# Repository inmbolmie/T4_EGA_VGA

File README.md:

# T4_EGA_VGA

Teensy 4.0 based CGA/EGA to VGA converter

_**Second version with improved shielding and protection**_

This is my poor-man's RGBi to VGA converter that can be built with just a Teensy 4.0 and a bunch of resistors. Works quite well with low resolution modes and works also but with a little less quality with high resolution modes. MDA is not supported at this moment.

To make it work you need as a bare minimum the Teensy 4.0, a VGA cable, a DE9 cable, and 25 resistors of 5 different values, so it can be made very cheaply as a DIY project on a breadboard.

The objective of this project was building the converter using only the Teensy, so it lacks any CPLD or other complex sampling and level shifting interfaces that other better converters like MCE2VGA use.

For the VGA output signal generation it uses the awesome VGA_t4 library by Jean-Marc Harvengt  https://github.com/Jean-MarcHarvengt/VGA_t4, this project wouldn't be possible without it.

Before jumping in, be sure that you have read the **current limitations** section and watch the video for an idea of its performance.

## Operation

The converter needs to be USB-powered through the Teensy micro-USB connector, from a computer port of a regular wall USB power adapter. If possible, it is better to power up the converter before connecting it to the video source.

Once the converter is powered, just connect the DE9 end to the computer/graphics card through a suitable cable to convert, and the DE15 end to the VGA monitor that will display the converted video signal. The DE9 cable mush be straight and all the pins must be connected. Try to avoid null modem or other special cables that are not straight pin-to-pin.

**Please, don't program the Teensy while connected to either the DE9 or DE15 connector.**

## Supported modes

Supported modes and some comments about each one.

http://minuszerodegrees.net/video/bios_video_modes.htm

|Mode|Resolution|VGA resolution|Scanlines|Supported|HR Switch|CPU Speed|Remarks|
|---	|---	|---	|---	|---	|---	|---	|---	|
|0x00h|320x200 greyscale|320x200|no|Resistor network*|off|600Mhz|40 columns text mode|
|0x01h|320x200 color|320x200|no|Resistor network*|off|600Mhz|40 columns text mode|
|0x02h|640x200 greyscale|640x480|yes|Level converter*|on|984Mhz|80 columns text mode|
|0x03h|640x200 color|640x480|yes|Level converter*|on|984Mhz|80 columns text mode|
|0x04h|320x200 color|320x200|no|Resistor network*|off|600Mhz|4 color CGA graphics|
|0x05h|320x200 greyscale|320x200|no|Resistor network*|off|600Mhz|4 gray CGA graphics|
|0x06h|640x200 monochrome|640x480|yes|Level converter*|on|984Mhz|CGA high res monochrome|
|0x07h|720x350 monochrome|NOT SUPPORTED|NOT SUPPORTED|NOT SUPPORTED|NOT SUPPORTED|NOT SUPPORTED|MDA monochrome mode|
|0x08h|160x200 color|UNTESTED|UNTESTED|UNTESTED|UNTESTED|UNTESTED|PCjr. mode, should work but untested|
|0x09h|320x200 color|UNTESTED|UNTESTED|UNTESTED|UNTESTED|UNTESTED|PCjr. mode, should work but untested|
|0x0Ah|640x200 color|UNTESTED|UNTESTED|UNTESTED|UNTESTED|UNTESTED|PCjr. mode, should work but untested|
|0x0Dh|320x200 color|320x200|no|Resistor network*|off|600Mhz|EGA 16 color low resolution|
|0x0Eh|640x200 color|640x480|yes|Level converter*|on|984Mhz|EGA 16 color high resolution|
|0x0Fh|640x350 monochrome|640x480|no|Level converter*|both|984Mhz|EGA monochrome ultra-high resolution|
|0x10h|640x350 color|640x480|no|Level converter*|both|984Mhz|EGA 16 color ultra-high resolution|

Notes:

**Resistor Network** This mode works with both board versions, with resistor network capture or level converter

**Level converter** This mode may work somehow with resistor network capture, but gives best results with the level converter version

## Screenshots

Some screenshots for the different supported modes. They are taken simply with a smartphone pointing to a modern IPS monitor, so the alignment isn't perfect but they can give and idea about how it works. The computer driving the display is an IBM 5160 with a Paradise EGA card.

## Videos

Video showing 350 lines text mode, the Checkit graphic tests, Monkey Island and Commander Keen in 320x200x16 mode and PlanetX3 in 640x350x16 mode. Yes, Monkey Island is slow, but that is because it is running in a poor IBM 5160, the converter operates always at the full 60Hz.

https://youtu.be/SZSuXO_p2-U

## Controls.

There are 4 buttons and 1 switch that can be used to adjust the converter operation. Those are optional and not strictly required for basic operation.

* **HR ON/OFF switch  (pin 14)**. When on, the 640x200 graphic and 80 columns text modes are enabled. That is needed because the signal specs for 320x200 and 640x200 modes are exactly the same, so the converter would have a bad day to try to distinguish between them. With the switch ON, 320x200 will work the same, but with the switch OFF 320x200 will work better and the Teensy will operate at stock speed (600Mhz) and wouldn't even need extra cooling.
* **Pixel adjustment decrease (pin 6)**. Decrease 1 unit the pixel alignment. This makes the sampling start earlier and is like displacing the picture to the right
* **Pixel adjustment increase (pin 5)**. Increase 1 unit the pixel alignment. This makes the sampling start later and is like displacing the picture to the left
* **Store pixel alignment (pin 7)**. Hold this button for 2 seconds to store the current pixel value in EEPROM. The autodiscovery will be disabled for the current mode.
* **Reboot/Reset (pin 9)**. Push to reboot the Teensy. Hold for 2 seconds to erase all stored pixel alignment values and reboot, the autodiscovery will be enabled for all modes.

## Current limitations:

This is an experimental converter so some amount of pain is expected.

* **Instability**. The Teensy running at overclocking frequencies isn’t the most stable thing in the world. Some sudden reboots are to be expected. Also you will have to reboot the Teensy sometimes when changing between graphics modes. Keep it cool.

* **Noise**. sampling is not perfect and will lead to some pixel noise here and there.

* **Color smearing**. There is a limitation, especially in high res, due to the way VGA_t4 works separating the color bits between two concurrent DMA transfers. This can lead to a phase difference between the color components and visible color smearing more evident in high contrast pictures.

* **Lost pixels**. Currently some pixels are lost in the right side of the image. I think those are sacrificed to get better picture quality tweaking the DMA transfer values. This can be either OK or unacceptable to you. You can get the pixels back tuning some VGA_t4 magic numbers, but then color smearing is exacerbated.

* **Line wobbling**. There is also a problem in that the moment the VGA line start is generated  is not 100% exact and the lines can wobble a little. This is quite evident at about 2/3 of the screen horizontally.

* **Artifacts**. Sampling is affected by the ISR and some pixels and lines are lost in the process. This is very evident in the 15,7Khz modes as the VGA signal is 31,5 Khz, almost exactly double the frequency so the artifacts happen twice per line and the affected pixels in one line are more or less the same than the line before and after. This generates horizontal (entire lines lost) and diagonal (lost pixels) black lines in each individual sampled picture. Example of a single screen capture for a 15,7Khz mode:

Thankfully the VGA horizontal frequency is not EXACTLY double the input horizontal frequency, because in that case the affected pixels will be always the same and a slow moving vertical black band would be always present in the picture, or if the band were around the HSYNC area you will get absolutely no picture at all.

The 21,8Khz modes are less affected and there is no visible interference pattern in the picture. Example of a single screen capture for this mode, where the small horizontal lines are the pixels lost due to the ISR firing:

* **No 720px modes**. Unfortunately VGA_t4 at the moment doesn’t support any 720px mode, so MDA (720x350) is not supported. If we ever get that mode, MDA should be perfectly possible as the pixel clock is the same as EGA.

* **Needs alignment for every different card**.  The key to get a nice picture is adjusting the exact clock cycle after HSYNC where the converter starts sampling the signal. This point varies among different modes and different graphic cards. For my EGA card in CGA mode the point is quite different to a real CGA card. With a converter that operates oversampling, or for an analog monitor this is not a problem because you simply reposition the image horizontally, that is sometimes automatically done by the monitor itself. The converter tries to guess the optimal sampling point automatically looking for the first pixel in the image and remembering it afterwards, but this can fail in some cases, like:

    * There are no pixels in the first column
 
    * Noise leads to a fake first pixel detection and you lose part of the image forever
 
    * Some clever programmers generate borders around the image that are falsely interpreted as pixels. This happens for instance with Commander Keen. 

Because all of this, the user can store using the control switches a value that overrides the automatic calculation if needed.

* **Initial sync is slow**. The adapter needs to sync to signals and generate the sampling tables programmatically, so it’s not the fastest thing out there.

* **Probably won’t work well with some cards**. If some graphics card for any reason doesn’t keep a steady on-spec pixel clock, the converter will fail miserably and vertical noise bands will develop where the sampling gets out of alignment. In those cases you can try to tweak the magic numbers for the graphic modes (pixel period, etc) but that is an absolutely DIY task.

## Internal working

The converter captures the EGA/CGA signal using synchronous sampling. The program synchronizes its execution with the HSYNC signal and counts clock cycles until the arrival of each pixel, then it samples the color signals in parallel and maps each sample to its pixel using precalculated tables based in the data about the specific graphics mode that is capturing. The pixel is then color translated to the right palette and stored in a framebuffer before the arrival of the next sample.

In parallel, the VGA_t4 module manages the generation of the VGA signal from the framebuffer through the DMA resources of the Teensy using a timed ISR to initiate the DMA transfers. The DMA transfer pumps data from the framebuffer and generates the lines of the VGA signals. That happens in parallel with the sampling code execution, except for the ISR itself. 

The ISR interrupts the sampling code each time it fires, that is once or twice per line, so some synchronization code is needed to detect the signal sampling intervals affected by the ISR and discard those pixels and sometimes entire lines from the captured signal. This generates some visible artifacts, especially in fast moving or flashing scenes in the 15,7Khz modes, but it is unavoidable with this arrangement. Maybe a future Teensy would support 3 concurrent DMA channels for FlexIO pins or full 8 bit I/O for the available channels, so that sampling could be implemented also with DMA.

The Teensy needs to be overclocked to be able to sample at the insane pixel rates of high resolution modes, (16,257Mhz for the EGA 10h mode). At this moment, the 640x200 and 640x350 modes need to operate at 984Mhz. The program adjusts the Teensy speed automatically as required for the input mode detected. Low resolution modes (320x200) work well at stock speed (600Mhz).

## Building software

Simply build the sketch with Arduino with the Teensyduino addon installed https://www.pjrc.com/teensy/td_download.html and upload it to a Teensy 4.0 via USB cable. I’ve used Arduino 1.8.13 and Teensyduino 1.5.3. Be sure that you compile it for 600Mhz and “fastest” compiler optimization.

## Circuits

### VGA signal generation

On the physical side, the digital to analog conversion to generate the VGA RGB signals is done using a simple R2R resistor ladder.  VGA_t4 supports up to 8 bit color (with an experimental 12 bit mode), but to get the EGA palette you only need 6 bit color, so a 6 bit ladder with 2 bits per color channel is used. 

This is the formula I used to calculate the resistor values. The objective for each color signal is getting from the 3,3V of the Teensy a 1,4V maximum level and 75 ohm output impedance, that will get converted to 0,7V when connecting to the VGA monitor and its 75 ohm terminations.

https://www.wolframalpha.com/input/?i=R2%2F%28R2%2B%282*%28R1%2F3%29%29%29+%3D+%281.4%2F3.3%29%2C+2*R1*R2%2F%283*%28R2%2B%282*R1%2F3%29%29%29%3D75

Given that calculations, I took as the final resistor values:

* 130 ohm for R2
* 255 ohm for R1 
* 510 ohm for 2R1, 

That should be close enough to the theoretical values. You can even use two 510 ohm resistors in parallel instead of the 255 ohm, or two 255 ohm in series instead of the 510 ohm, so that one less resistor value is required. This won’t win any color accuracy competition, but should be good enough.

### EGA/CGA input capture

Unfortunately, for the EGA/CGA signal sampling we need to make voltage conversion, as EGA/CGA is TTL signalling with a 5V logic level, and the Teensy 4 only supports a maximum of 3,3V in its input pins. Give them the full 5V and you will fry the poor thing. 

To overcome that there are different possible solutions, and I have selected two, one using only a resistor network and the other making use of an active voltage converter.

### Version one: Cheapo resistor divider.

The true poor-man’s alternative. As the IBM CGA card line drivers are 74LS244 IC’s I calculate the minimum series resistor value from a (very optimistic, probably overestimated) 1mA maximum theoretical output current for the TTL gate. That gives for the 5V signal a maximum load of 5 Kohm. To get 3,3V from 5V through a 5K resistor divider you can use approximately a 1,5K and a 3K resistor.

This approach is cheap and easy, but it has the drawback that the resistors act like a RC network, slowing down the transitions between the high and low logical levels as the retain charge stored in the parasitic capacitance of the wires and the resistors themselves, that need to be discharged through the resistors. That flattens the signal and generates slow rising and falling edges that affect the sampling.

So with a resistor network you can expect the converter to operate like this:

* Low resolution (320X200 graphic and 40 columns text) modes work quite well. Pixel clock is around 8Mhz, slow enough for the resistor network to operate acceptably.

* High resolution text modes (80 columns) are usable with noise.    

* High resolution graphic modes work acceptable with less demanding games that doesn’t use complex graphics (like Thexder)

* High resolution graphic modes with more complex games like PlanetX3 (EGA version) work like crap. This is due to the fact that Planet X3 makes heavy use of dithering in high resolution modes, and that dithering generates a very high frequency in the color channels (16Mhz) that is basically too much for the resistor network.

If you are adventurous enough the quality can be quite improved lowering the resistor values, BUT that comes with the risk of overloading the line drivers of the graphics card or degrading the signal levels, so be warned if you try that.

Also be sure that you double check the resistor network wiring, as there is a risk the Teensy could receive the full 5V if something is wired up wrongly.

### Version two: TXS0108E voltage translator.

This is a popular bidirectional voltage translator for microcontrollers that theoretically can accept up to 55Mhz signals. It has just the 8 channels we need for the conversion (6 colors plus HSYNC and VSYNC). With this in place all the modes, high and low resolution work quite well. As it is popular it can be obtained very cheaply and you can even get it mounted in a nice ready to plug prototype board.

I’ve tried other solutions, none of which was fully satisfactory:

**74HCT245 driver @5V plus a lower value (500 ohm) resistor divider.** The 74HCT can drive higher loads than the 74LS so we can significantly lower the resistor values. Works well, but too cumbersome as you need the active component PLUS the resistors to make the 5V-3.3V conversion.

**74LVC245 driver @3,3V.** Too noisy, sampling gives terrible quality.

**74FCT244 driver**, quite rubbish sampling quality, didn’t work at all.

I haven’t tried one other possible solution, that is connect the signals to the Teensy through a single current limiting series resistor per channel. That is for the most adventurous out there, I haven’t tried because I don’t want to ruin my only Teensy board, but it should be possible if the right resistor value is low enough to get a good signal and high enough not to fry the Teensy. No idea of what that value should be.

## Schematics

### Schematic for version 1, TXS0108E based capture solution.

### Schematic for version 2, resistor based capture solution.

## Board fabrication

If you are crazy enough to make a real PCB for this, I provide the needed resources for the TXS0108E version, gerber file, bom and component placement for a popular online fabricator.

## Q&A:

**Is this better than a MCE2VGA?**

Definitely no, this is hackish and the MCE2VGA is very professional. You will have to adjust the sampling alignment all the time, the image quality is much worse and it supports less input modes and resolutions. Not to mention you can get a MCE2VGA tested, assembled and inside a nice 3D printed case for a reasonable amount of money.

**Should I use this as my main converter for my retro hardware?**

I see this as a nice weekend mini-project if you already have the Teensy, a bunch of resistors, you like it and you have no high expectations. I don’t recommend going for it as a standalone converter for general use.

**Why do you repeat so much code? Have you ever heard about functions and parameters?**

Of course I’ve heard, but in this case the code performance is absolutely critical. You have a fixed amount of clock cycles to process each sample before the next sample arrives. Some sections simply don’t work fast enough unless you use constants instead of variables, and reduce loops and logic checks to the bare minimum. And that is even more complicated by the VGA ISR firing all the time and interfering with the sampling. So I need/prefer to keep the modes all separated in code, despite 99% of that code being identical between different modes. Maybe some assembly code would help but actually it is working without needing any. Maybe that could make high resolution modes work at lower clock frequencies.

**Could this converter kill my beloved vintage graphics card/computer/monitor?**

Yes it can. I’ve not been able to test it with much hardware, I only have an IBM CGA card and a Paradise EGA card to test the converter, and with those it works flawlessly, but who knows with others.

**Could this converter kill my Teensy?**

High resolution modes work only with the Teensy overclocked at very high speeds (984Mhz), so you absolutely need to run the Teensy with some cooling in place, and there is a certain risk it will become unstable, be killed in action, catch fire, explode, or generate a mini black hole. The low resolution modes work at stock speed (600Mhz) so they are much more friendly.

**Why don’t you also use DMA for sampling, like VGA_t4 does for VGA signal generation?**

Because the DMA resources are limited and they are already taken for VGA signal generation. FlexIO1 and FlexIO2 ports are already taken and FlexIO3 doesn’t support DMA operation. Also it would be much more difficult to manage sampling alignment and it is absolutely critical for proper operation, and I suppose that you don’t have as much control over the DMA precise timings once a transfer is initiated. For the VGA signal, some out of alignment will make no difference at all but for synchronous sampling that is unacceptable.

**Why don’t you sample at higher rates? Have you heard about Nyquist?**

I think commercial FPGA based solutions sample at like 4xNyquist near 130Mhz, so they can get a very precise alignment and give a very high image quality that way, but that rates are simply out of reach for a Teensy or any microcontroller today in existence, so other strategies need to be used to make it work without specialized hardware like the MCE2VGA or Raspberry pi zero + CPLD solution do.

## Details about graphic modes definition.

If you want to tinker with the magic numbers, this is an explanation about each one.

```
//CLOCK AND SAMPLING MODES
//UNCOMMENT JUST ONE BLOCK FOR EACH MODE (200, 200_HR, 350)

//STOCK 600Mhz 200 LINES PARADISE EGA
/**/
const String NAME_200_COLOR = "Mode 320x200x16 @60";
const int MIN_CYCLES_HSYNC_200_COLOR  = 38169  ;
const int CYCLES_HSYNC_HIRES_200_COLOR = 38000  ;
const int CYCLES_FIRST_PIXEL_200_COLOR  = 7480; 
const int CYCLES_PIXEL_200_COLOR  = 84  ;
const int CYCLES_PIXEL_200_COLOR_EXACT = 83811  ;
const int CYCLES_HALF_PIXEL_200_COLOR_EXACT = 41905 ;
const int CYCLES_HALF_PIXEL_200_COLOR = 42  ;
const int CYCLES_PIXEL_200_COLOR_MAX_SKEW = 20  ;
const int CYCLES_PIXEL_200_COLOR_PRESAMPLE = 0;
const int CYCLES_2_PIXEL_200_COLOR = 168  ;
const int MAX_CYCLES_VSYNC_200_COLOR = 10020020 ;
const int MIN_CYCLES_VSYNC_200_COLOR = 10000000  ;
const int BLANK_LINES_SCREEN_200_COLOR = 36  ;
const int LINES_200_LINES = 200 ;
const int PIXELS_200_LINES = 320;
const int SCANLINES_200_LINES = 2;
const unsigned long CPU_FREQ_200_LINES  = 600000000;
const vga_mode_t VGA_MODE_200_LINES = VGA_MODE_320x480;
```

* NAME: Name for the mode that will be displayed in the OSD
* CPU_FREQ: Teensy will be configured to run at this clock speed in this mode. This value affects all the others as it has to be taken into account in their calculations
* MIN_CYCLES_HSYNC: minimum acceptable period of the HSYNC signal in clock cycles
* CYCLES_HSYNC_HIRES: cycles since last HSYNC when we will start to seek actively the following HSYNC
* CYCLES_FIRST_PIXEL: Default position in clock cycles after the last HSYNC edge where we will sample the first pixel. This value is not used if autodiscovery is enabled or a user value is stored. This is a key value and is much dependent on the particular hardware and graphic mode.
* CYCLES_PIXEL: Clock cycles between consecutive pixels. This value is rounded to an integer
* CYCLES_PIXEL_EXACT: Clock cycles between consecutive pixels measured in millicycles
* CYCLES_HALF_PIXEL: Half the clock cycles between consecutive pixels. This value is rounded to an integer
* CYCLES_HALF_PIXEL_EXACT: Half the clock cycles between consecutive pixels measured in millicycles
* CYCLES_PIXEL_MAX_SKEW: Any sample that is early or late by more than this amount of clock cycles will be discarded
* CYCLES_PIXEL_PRESAMPLE: As the sampling mechanism is released by a loop that takes itself some clock cycles to process, it’s not always possible to get accurately to the sampling point. This value allows releasing the loop earlier by the given amount of clock cycles to try to get to the sampling point more accurately.
* MAX_CYCLES_VSYNC : maximum acceptable period of the VSYNC signal in clock cycles
* MIN_CYCLES_VSYNC : minimum acceptable period of the VSYNC signal in clock cycles
* BLANK_LINES_SCREEN: Number of empty lines that will be ignored after VSYNC
* PIXELS: Pixels per line that will be captured
* SCANLINES: 1-> no scanlines; 2-> an empty line will be added in the output for each captured line
* VGA_MODE: Output mode the VGA_t4 output will be put in for this input mode

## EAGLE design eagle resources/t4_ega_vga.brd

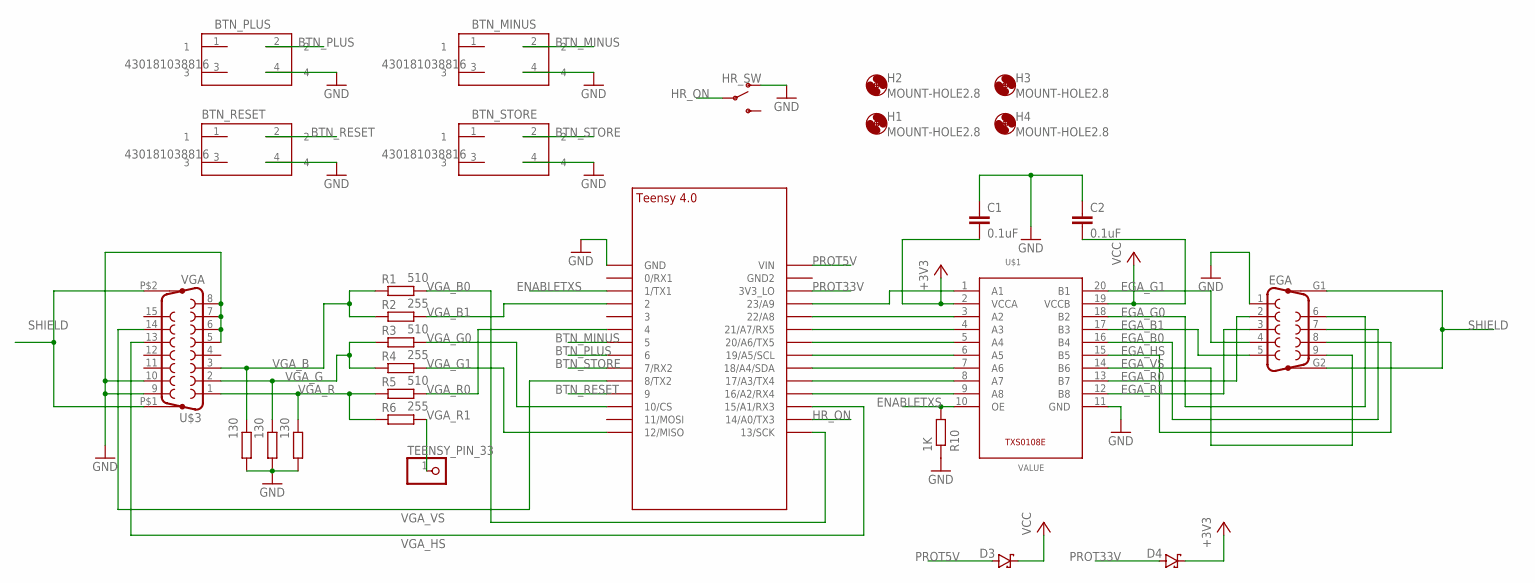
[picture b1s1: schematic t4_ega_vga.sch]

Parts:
BTN_MINUS: 430181038816
BTN_PLUS: 430181038816
BTN_RESET: 430181038816
BTN_STORE: 430181038816
C1, C2: 0.1uF; C0603
D3, D4: SMA-SS34-SYMBOL; SMA-SS34
EGA: F09HP
H1, H2, H3, H4: MOUNT-HOLE2.8; 2,8
HR_SW: SWITCH-SPDT-SMD-RIGHT-ANGLE; SWITCH_SPST_SMD_A
R1, R3, R5: 510; R0603
R2, R4, R6: 255; R0603
R7, R8, R9: 130; R0603
R10: 1K; R0603
TEENSY_PIN_33: PINHD-1X1; 1X01
U2: TEENSY_4.0-BASIC
U$1: TXS0108E; TSSOP20
U$3: VGA; HDF15H

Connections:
+3V3: C1.2, D4.2 (K), U$1.2 (VCCA)
BTN_MINUS: BTN_MINUS.2, U2.5
BTN_PLUS: BTN_PLUS.2, U2.6
BTN_RESET: BTN_RESET.2, U2.9/CS (9)
BTN_STORE: BTN_STORE.2, U2.7 (7/RX2)
EGA_B0: EGA.7, U$1.16 (B4)
EGA_B1: EGA.5, U$1.17 (B3)
EGA_G0: EGA.6, U$1.18 (B2)
EGA_G1: EGA.4, U$1.20 (B1)
EGA_HS: EGA.8, U$1.15 (B5)
EGA_R0: EGA.2, U$1.13 (B7)
EGA_R1: EGA.3, U$1.12 (B8)
EGA_VS: EGA.9, U$1.14 (B6)
ENABLETXS: R10.2, U2.1/TX (1/TX1), U$1.10 (OE)
GND: BTN_MINUS.4, BTN_PLUS.4, BTN_RESET.4, BTN_STORE.4, C1.1, C2.1, EGA.1, HR_SW.1 (O), R7.1, R8.1, R9.1, R10.1, U2.GND, U$1.11 (GND), U$3.5, U$3.6, U$3.7, U$3.8, U$3.9, U$3.10
HR_ON: HR_SW.2, U2.14/A0 (14/A0/TX3)
unnamed: U2.23/A9, U$1.1 (A1)
unnamed: U2.22/A8, U$1.3 (A2)
unnamed: U2.21/A7 (21/A7/RX5), U$1.4 (A3)
unnamed: U2.20/A6 (20/A6/TX5), U$1.5 (A4)
unnamed: U2.19/A5/SCL, U$1.6 (A5)
unnamed: U2.18/A4/SDA, U$1.7 (A6)
unnamed: U2.17/A3 (17/A3/TX4), U$1.8 (A7)
unnamed: U2.16/A2 (16/A2/RX4), U$1.9 (A8)
PROT5V: D3.1 (A), U2.VIN
PROT33V: D4.1 (A), U2.3V3_LO
SHIELD: EGA.G1, EGA.G2, U$3.P$1 (G1), U$3.P$2 (G2)
VCC: C2.2, D3.2 (K), U$1.19 (VCCB)
VGA_B: R1.1, R2.1, R7.2, U$3.3
VGA_B0: R1.2, U2.13/SCK
VGA_B1: R2.2, U2.2
VGA_G: R3.1, R4.1, R8.2, U$3.2
VGA_G0: R3.2, U2.10/CS
VGA_G1: R4.2, U2.12/MISO
VGA_HS: U2.15/A1 (15/A1/RX3), U$3.13
VGA_R: R5.1, R6.1, R9.2, U$3.1
VGA_R0: R5.2, U2.4/CANRX (4)
VGA_R1: R6.2, TEENSY_PIN_33.1
VGA_VS: U2.8 (8/TX2), U$3.14

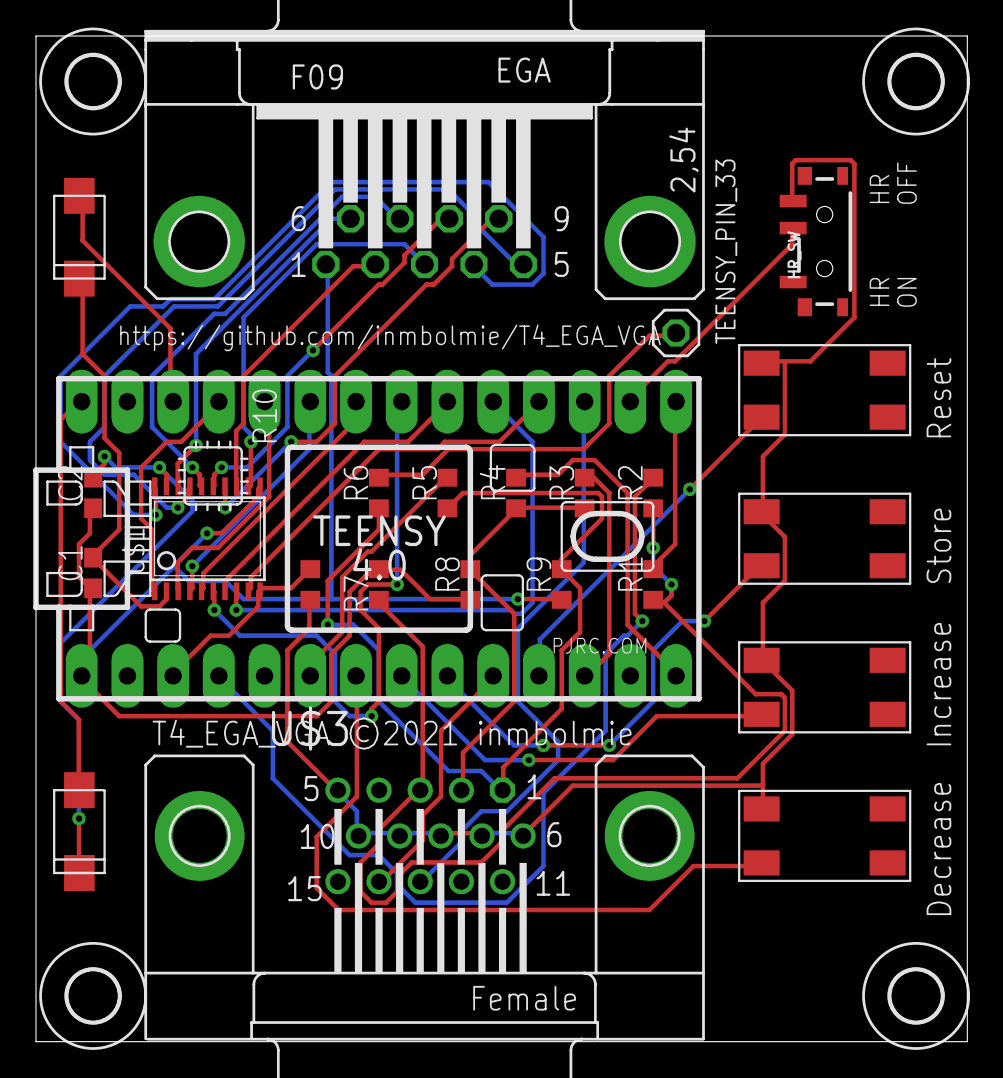
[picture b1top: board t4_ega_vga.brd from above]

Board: 2 copper layers, 51.7 x 55.9 mm, 28 parts (0 on the bottom side), 39 nets.

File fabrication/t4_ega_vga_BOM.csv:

Comment,Designator,Footprint,LCSC Part #
0.1uF,HR_SW C1 C2,C0603,
1K,R10,R0603,
130,R7 R8 R9,R0603,
255,R2 R4 R6,R0603,
510,R1 R3 R5,R0603,
430181038816,BTN_MINUS BTN_PLUS BTN_RESET BTN_STORE,430181038816,
SMA-SS34-SYMBOL,D3 D4,SMA-SS34,
TXS0108E,U1,TSSOP20,

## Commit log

2021-02-27 Create x
2021-02-27 Arduino code first version
2021-02-28 Hack to improve 350 lines mode
2021-03-02 Disabling debug output also disabled OSD
2021-03-06 Update README.md
    Warning
2021-03-07 Fixed CGA palette as in the last version of the hardware the NC signal becomes fixed high
2021-03-09 Reviewing board design
2021-11-05 revised schematics and fabrication files
2021-11-05 revised schematics

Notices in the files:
eagle resources/t4_ega_vga.brd:
T4_EGA_VGA ©2021 inmbolmie
parts and their libraries:
Wurth_Elektronik_Electromechanic_Switchs: Copyright: Würth Elektronik
SparkFun-Switches: Licensing: Creative Commons ShareAlike 4.0 International - https://creativecommons.org/licenses/by-sa/4.0
